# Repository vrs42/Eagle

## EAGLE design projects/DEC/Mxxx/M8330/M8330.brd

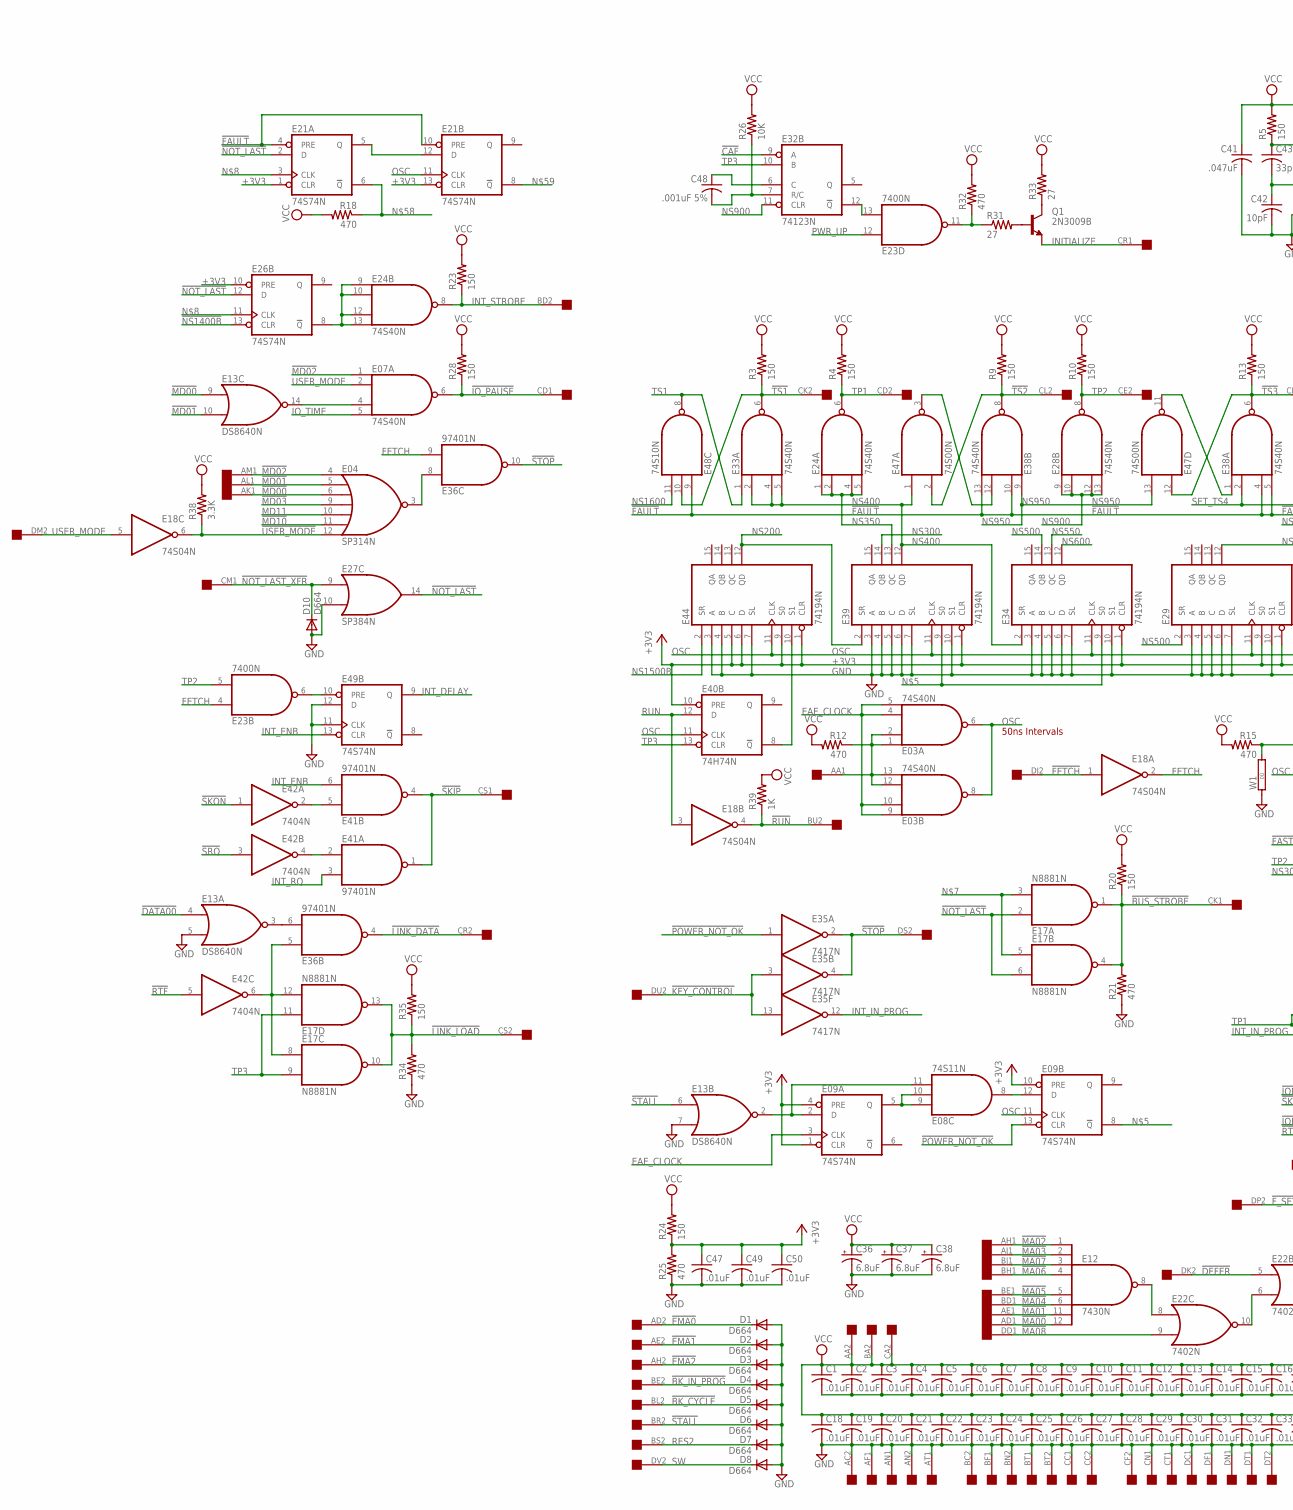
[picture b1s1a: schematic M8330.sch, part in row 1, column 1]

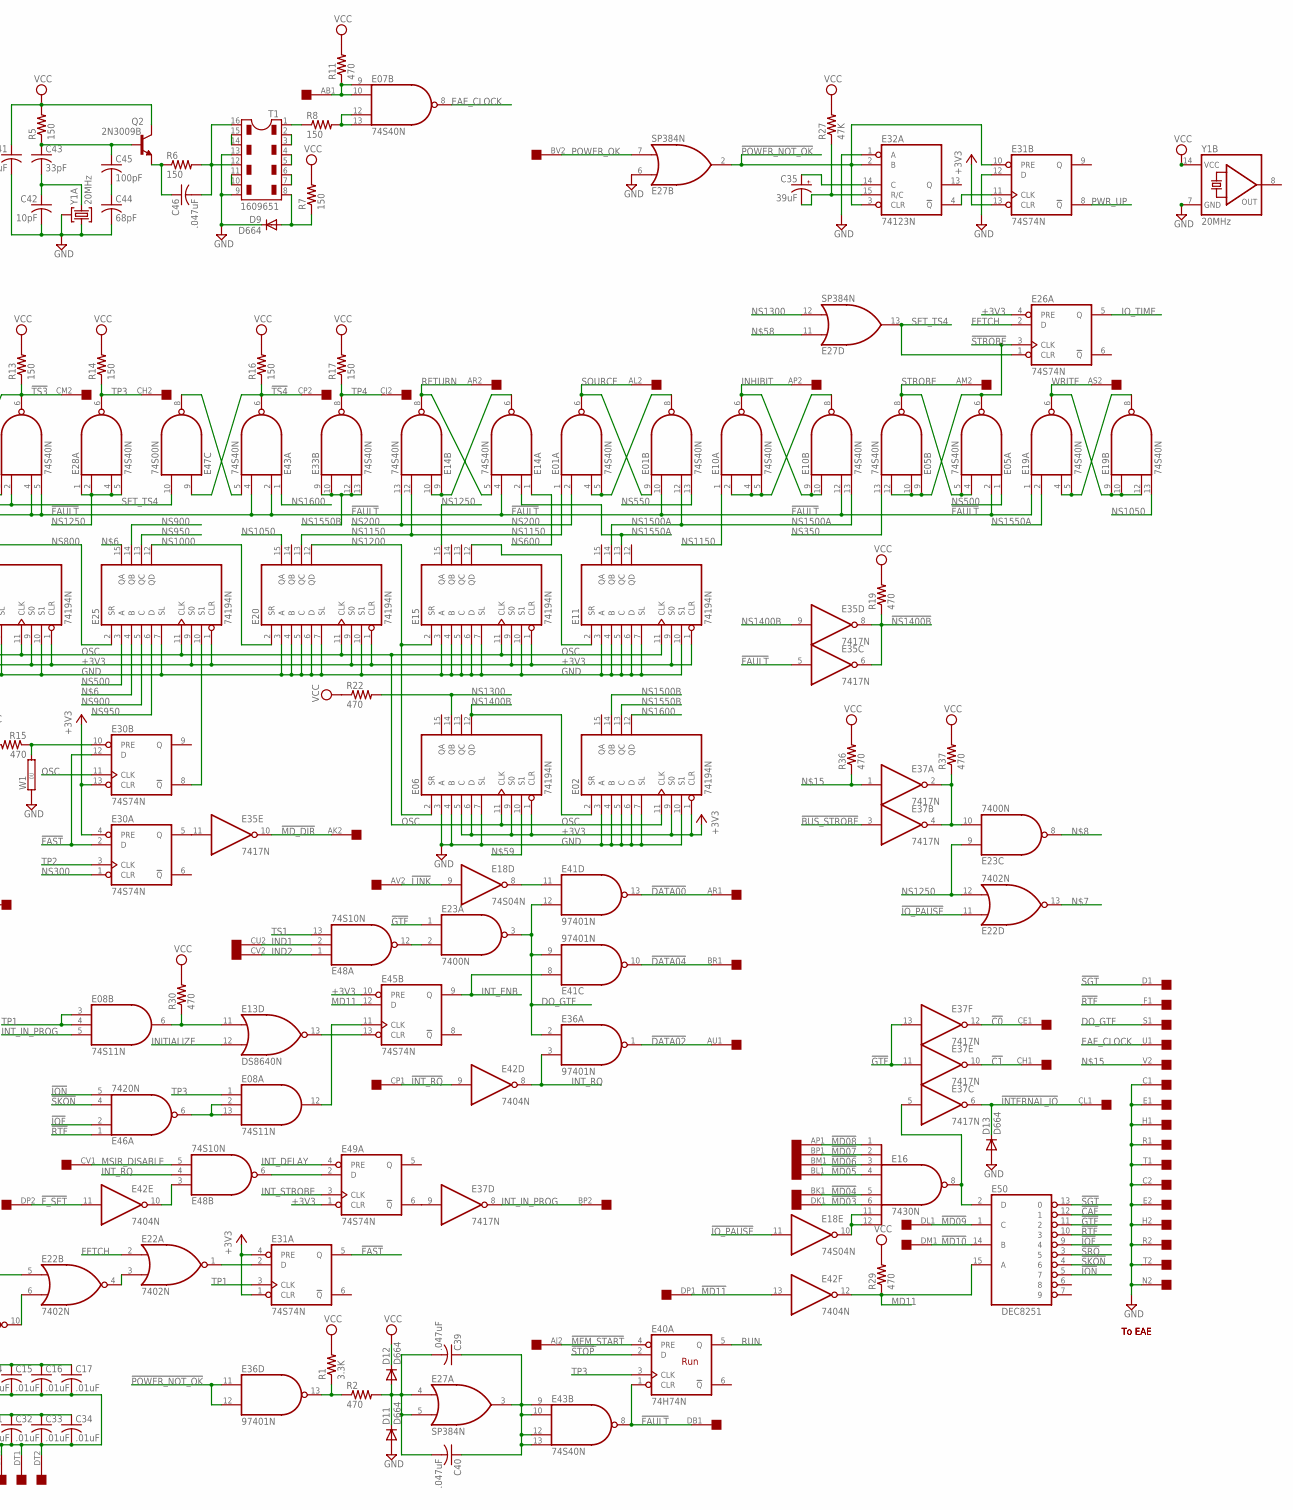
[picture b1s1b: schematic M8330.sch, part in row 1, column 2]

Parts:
C1, C2, C3, C4, C5, C6, C7, C8, C9, C10, C11, C12, C13, C14, C15, C16, C17, C18, C19, C20, C21, C22, C23, C24, C25, C26, C27, C28, C29, C30, C31, C32, C33, C34, C47, C49, C50: .01uF; C050-025X075
C35: 39uF; E12-8
C36, C37, C38: 6.8uF; E12-8
C39, C40, C41, C46: .047uF; C050-025X075
C42: 10pF; C050-025X075
C43: 33pF; C050-025X075
C44: 68pF; C050-025X075
C45: 100pF; C050-025X075
C48: .001uF 5%; C050-025X075
D1, D2, D3, D4, D5, D6, D7, D8, D9, D10, D11, D12, D13: D664; DO35-10
E01, E03, E05, E07, E10, E14, E19, E24, E28, E33, E38, E43: 74S40N; DIL14
E02, E06, E11, E15, E20, E25, E29, E34, E39, E44: 74194N; DIL16
E04: SP314N; DIL14
E08: 74S11N; DIL14
E09, E21, E26, E30, E31, E45, E49: 74S74N; DIL14
E12, E16: 7430N; DIL14
E13: DS8640N; DIL14
E17: N8881N; DIL14
E18: 74S04N; DIL14
E22: 7402N; DIL14
E23: 7400N; DIL14
E27: SP384N; DIL14
E32: 74123N; DIL16
E35, E37: 7417N; DIL14
E36, E41: 97401N; DIL14
E40: 74H74N; DIL14
E42: 7404N; DIL14
E46: 7420N; DIL14
E47: 74S00N; DIL14
E48: 74S10N; DIL14
E50: DEC8251; DIL16
J: SINGLE; EDGE-CON2
Q1, Q2: 2N3009B; TO5
R1, R38: 3.3K; 0207/10
R2, R11, R12, R15, R18, R19, R21, R22, R25, R29, R30, R32, R34, R36, R37: 470; 0207/10
R3, R4, R5, R6, R7, R8, R9, R10, R13, R14, R16, R17, R20, R23, R24, R28, R35: 150; 0207/10
R26: 10K; 0207/10
R27: 47K; 0207/10
R31, R33: 27; 0207/10
R39: 1K; 0207/10
T1: 1609651; DIL16
U$2: QUAD; EDGE-CON8
W1: 0R; 0R/10
Y1A: 20MHz; HC49TL-H
Y1B: 20MHz; DIL14S

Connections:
!BK_CYCLE: D5.C, U$2.BL2
!BK_IN_PROG: D4.C, U$2.BE2
!BUS_STROBE: E17.1 (O), E17.4 (O), E37.3 (I), R20.1, R21.2, U$2.CK1
!C0: E37.12 (O), U$2.CE1
!C1: E37.10 (O), U$2.CH1
!CAF: E32.9 (A), E50.12 (1)
!DATA00: E13.4 (I0), E41.13 (O), U$2.AR1
!DATA02: E36.1 (O), U$2.AU1
!DATA04: E41.10 (O), U$2.BR1
!DEFER: E22.5 (I0), U$2.DK2
!EMA0: D1.C, U$2.AD2
!EMA1: D2.C, U$2.AE2
!EMA2: D3.C, U$2.AH2
!FAST: E30.2 (D), E30.12 (D), E31.5 (Q)
!FAULT: E01.10 (I1), E05.2 (I1), E10.12 (I2), E14.4 (I2), E19.1 (I0), E21.4 (PRE), E21.10 (PRE), E35.5 (I), E38.4 (I2), E38.5 (I3), E38.10 (I1), E38.13 (I3), E40.1 (CLR), E43.2 (I1), E43.4 (I2), E43.8 (O), E48.9 (I0), U$2.DB1
!FETCH: E18.1 (I), U$2.DJ2
!F_SET: E42.11 (I), U$2.DP2
!GTF: E23.1 (I0), E37.11 (I), E37.13 (I), E50.11 (2)
!INTERNAL_IO: D13.C, E37.6 (O), U$2.CL1
!INT_RQ: E42.9 (I), U$2.CP1
!IOF: E46.2 (I1), E50.9 (4)
!ION: E46.5 (I3), E50.5 (7)
!IO_PAUSE: E07.6 (O), E18.11 (I), E22.11 (I0), R28.1, U$2.CD1
!KEY_CONTROL: E35.3 (I), E35.13 (I), U$2.DU2
!LINK: E18.9 (I), U$2.AV2
!LINK_DATA: E36.4 (O), U$2.CR2
!LINK_LOAD: E17.10 (O), E17.13 (O), R34.2, R35.1, U$2.CS2
!MA00: E12.12 (I7), U$2.AD1
!MA01: E12.11 (I6), U$2.AE1
!MA02: E12.1 (I0), U$2.AH1
!MA03: E12.2 (I1), U$2.AJ1
!MA04: E12.6 (I5), U$2.BD1
!MA05: E12.5 (I4), U$2.BE1
!MA06: E12.4 (I3), U$2.BH1
!MA07: E12.3 (I2), U$2.BJ1
!MA08: E22.9 (I1), U$2.DD1
!MD00: E04.6 (I2), E13.9 (I0), U$2.AK1
!MD01: E04.5 (I1), E13.10 (I1), U$2.AL1
!MD02: E04.4 (I0), E07.1 (I0), U$2.AM1
!MD03: E04.9 (I3), E16.6 (I5), U$2.DK1
!MD04: E16.5 (I4), U$2.BK1
!MD05: E16.4 (I3), U$2.BL1
!MD06: E16.3 (I2), U$2.BM1
!MD07: E16.2 (I1), U$2.BP1
!MD08: E16.1 (I0), U$2.AP1
!MD09: E50.1 (C), U$2.DL1
!MD10: E04.11 (I5), E50.14 (B), U$2.DM1
!MD11: E42.13 (I), U$2.DP1
!MD_DIR: E35.10 (O), U$2.AK2
!MEM_START: E40.4 (PRE), U$2.AJ2
!NOT_LAST: E17.2 (I0), E17.6 (I1), E21.2 (D), E26.12 (D), E27.14 (O)
!NOT_LAST_XFR: D10.C, E27.9 (I0), U$2.CM1
!NS1400B: E26.13 (CLR), E35.6 (O), E35.8 (O), R19.1
!POWER_NOT_OK: E09.13 (CLR), E27.2 (O), E31.10 (PRE), E32.2 (B), E32.3 (CLR), E35.1 (I), E36.11 (I0), E36.12 (I1)
!RTF: E42.5 (I), E46.1 (I0), E50.10 (3), J.F1
!RUN: E18.4 (O), R39.1, U$2.BU2
!SGT: E50.13 (0), J.D1
!SKIP: E41.1 (O), E41.4 (O), U$2.CS1
!SKON: E42.1 (I), E46.4 (I2), E50.4 (6)
!SRQ: E42.3 (I), E50.3 (5)
!STALL: D6.C, E13.6 (I0), U$2.BR2
!STOP: E35.2 (O), E35.4 (O), E36.10 (O), E40.2 (D), U$2.DS2
!STROBE: E05.6 (O), E05.9 (I0), E05.10 (I1), E05.12 (I2), E26.3 (CLK)
!TS1: E33.6 (O), E48.10 (I1), R3.1, U$2.CK2
!TS2: E38.8 (O), E47.2 (I1), R9.1, U$2.CL2
!TS3: E38.6 (O), E47.12 (I0), R13.1, U$2.CM2
!TS4: E43.6 (O), E47.9 (I0), R16.1, U$2.CP2
!USER_MODE: E04.12 (I6), E18.6 (O), R38.1
+3V3: C47.1, C49.1, C50.1, E02.1 (CLR), E02.9 (S0), E06.1 (CLR), E06.5 (C), E06.6 (D), E06.9 (S0), E09.1 (CLR), E09.4 (PRE), E09.10 (PRE), E11.1 (CLR), E11.9 (S0), E15.1 (CLR), E15.9 (S0), E20.1 (CLR), E20.9 (S0), E21.1 (CLR), E21.13 (CLR), E25.1 (CLR), E25.9 (S0), E26.4 (PRE), E26.10 (PRE), E29.1 (CLR), E29.9 (S0), E30.4 (PRE), E30.13 (CLR), E31.1 (CLR), E31.4 (PRE), E31.13 (CLR), E34.1 (CLR), E39.1 (CLR), E40.10 (PRE), E44.1 (CLR), E44.5 (C), E44.6 (D), E44.9 (S0), E45.10 (PRE), E49.1 (CLR), R24.1, R25.2
DO_GTF: E23.3 (O), E36.2 (I0), E41.9 (I1), E41.12 (I1), J.S1
EAE_CLOCK: E03.4 (I2), E03.5 (I3), E03.9 (I0), E03.10 (I1), E07.8 (O), E09.3 (CLK), J.U1
FETCH: E18.2 (O), E22.2 (I0), E23.4 (I0), E26.2 (D), E36.9 (I1)
F_SET: E42.10 (O), E48.3 (I0)
GND: C1.2, C2.2, C3.2, C4.2, C5.2, C6.2, C7.2, C8.2, C9.2, C10.2, C11.2, C12.2, C13.2, C14.2, C15.2, C16.2, C17.2, C18.2, C19.2, C20.2, C21.2, C22.2, C23.2, C24.2, C25.2, C26.2, C27.2, C28.2, C29.2, C30.2, C31.2, C32.2, C33.2, C34.2, C36.-, C37.-, C38.-, C41.2, C42.2, C44.2, C47.2, C49.2, C50.2, D1.A, D2.A, D3.A, D4.A, D5.A, D6.A, D7.A, D8.A, D9.C, D10.A, D11.A, D13.A, E01.7 (GND), E02.3 (A), E02.4 (B), E02.5 (C), E02.6 (D), E02.7 (SL), E02.8 (GND), E02.10 (S1), E03.7 (GND), E04.1 (GND), E05.7 (GND), E06.3 (A), E06.4 (B), E06.7 (SL), E06.8 (GND), E07.7 (GND), E08.7 (GND), E09.7 (GND), E10.7 (GND), E11.3 (A), E11.4 (B), E11.5 (C), E11.6 (D), E11.7 (SL), E11.8 (GND), E11.10 (S1), E12.7 (GND), E13.1 (GND), E13.5 (I1), E13.7 (I1), E14.7 (GND), E15.3 (A), E15.4 (B), E15.5 (C), E15.6 (D), E15.7 (SL), E15.8 (GND), E15.10 (S1), E16.7 (GND), E17.7 (GND), E18.7 (GND), E19.7 (GND), E20.3 (A), E20.4 (B), E20.5 (C), E20.6 (D), E20.7 (SL), E20.8 (GND), E20.10 (S1), E21.7 (GND), E22.7 (GND), E23.7 (GND), E24.7 (GND), E25.7 (SL), E25.8 (GND), E26.7 (GND), E27.1 (GND), E27.6 (I0), E27.10 (I1), E28.7 (GND), E29.3 (A), E29.4 (B), E29.5 (C), E29.6 (D), E29.7 (SL), E29.8 (GND), E29.10 (S1), E30.7 (GND), E31.7 (GND), E31.12 (D), E32.1 (A), E32.8 (GND), E33.7 (GND), E34.3 (A), E34.4 (B), E34.5 (C), E34.6 (D), E34.7 (SL), E34.8 (GND), E34.10 (S1), E35.7 (GND), E36.7 (GND), E37.7 (GND), E38.7 (GND), E39.3 (A), E39.4 (B), E39.5 (C), E39.6 (D), E39.7 (SL), E39.8 (GND), E39.10 (S1), E40.7 (GND), E41.7 (GND), E42.7 (GND), E43.7 (GND), E44.3 (A), E44.4 (B), E44.7 (SL), E44.8 (GND), E45.7 (GND), E46.7 (GND), E47.7 (GND), E48.7 (GND), E49.7 (GND), E49.11 (CLK), E49.12 (D), E50.8 (GND), J.C1, J.C2, J.E1, J.E2, J.H1, J.H2, J.N2, J.R1, J.R2, J.T1, J.T2, R21.1, R25.1, R34.1, T1.9, T1.13, U$2.AC2, U$2.AF1, U$2.AN1, U$2.AN2, U$2.AT1, U$2.BC2, U$2.BF1, U$2.BN2, U$2.BT1, U$2.BT2, U$2.CC1, U$2.CC2, U$2.CF2, U$2.CN1, U$2.CT1, U$2.DC1, U$2.DF1, U$2.DN1, U$2.DT1, U$2.DT2, W1.1, Y1A.1, Y1A.3, Y1B.7 (GND)
IND1: E48.2 (I1), U$2.CU2
IND2: E48.1 (I0), U$2.CV2
INHIBIT: E10.6 (O), E10.9 (I0), E10.10 (I1), U$2.AP2
INITIALIZE: E13.12 (I1), Q1.1 (E), U$2.CR1
INT_DELAY: E49.4 (PRE), E49.9 (Q)
INT_ENB: E41.6 (I1), E41.8 (I0), E45.9 (Q), E49.13 (CLR)
INT_IN_PROG: E08.5 (I2), E35.12 (O), E37.8 (O), U$2.BP2
INT_RQ: E36.3 (I1), E41.3 (I1), E42.8 (O), E48.4 (I1)
INT_STROBE: E24.8 (O), E49.3 (CLK), R23.1, U$2.BD2
IO_TIME: E07.5 (I3), E26.5 (Q)
MD11: E04.10 (I4), E42.12 (O), E45.12 (D), E50.15 (A), R29.1
MSIR_DISABLE: E48.5 (I2), U$2.CV1
unnamed: E16.8 (O), E37.5 (I), E50.2 (D)
unnamed: E23.10 (I1), E37.2 (O), E37.4 (O), R37.1
unnamed: E04.3 (O), E36.8 (I0)
unnamed: E40.8 (!Q), E44.10 (S1)
unnamed: E09.8 (!Q), E34.9 (S0), E39.9 (S0)
unnamed: E25.4 (B), E25.15 (QA)
unnamed: E17.3 (I1), E17.5 (I0), E22.13 (O)
unnamed: E21.3 (CLK), E23.8 (O), E26.11 (CLK)
unnamed: E18.8 (O), E41.11 (I0)
unnamed: C42.1, C43.2, Y1A.2
unnamed: E03.1 (I0), E03.2 (I1), E03.12 (I2), E03.13 (I3), R12.1, U$2.AA1
unnamed: E07.9 (I0), E07.10 (I1), R11.1, U$2.AB1
unnamed: E12.8 (O), E22.8 (I0)
unnamed: E37.1 (I), J.V2, R36.1
unnamed: E08.11 (I2), E09.2 (D), E13.2 (O)
unnamed: C48.2, E32.7 (R/C), R26.1
unnamed: E16.11 (I6), E16.12 (I7), E18.10 (O)
unnamed: E23.13 (I1), E32.12 (!Q)
unnamed: C48.1, E32.6 (C)
unnamed: Q1.3 (C), R33.1
unnamed: Q1.2 (B), R31.2
unnamed: E23.11 (O), R31.1, R32.1
unnamed: E31.11 (CLK), E32.4 (!Q)
unnamed: C43.1, C45.1, Q2.2 (B), R5.1
unnamed: C39.1, C40.1, E27.3 (O), E43.9 (I0), E43.10 (I1), E43.12 (I2), E43.13 (I3)
unnamed: C39.2, C40.2, D11.C, D12.A, E27.4 (I0), E27.5 (I1), R2.2
unnamed: C46.2, R6.2, T1.12, T1.16
unnamed: E36.13 (O), R1.1, R2.1
unnamed: C44.1, C45.2
unnamed: C46.1, Q2.1 (E), R6.1
unnamed: R8.1, T1.1
unnamed: T1.10, T1.11
unnamed: T1.6, T1.7
unnamed: T1.14, T1.15
unnamed: T1.2, T1.3
unnamed: T1.4, T1.5
unnamed: D9.A, R7.1, T1.8
unnamed: E07.12 (I2), E07.13 (I3), R8.2
unnamed: E22.6 (I1), E22.10 (O)
unnamed: E08.9 (I0), E08.10 (I1), E09.5 (Q)
unnamed: E08.8 (O), E09.12 (D)
unnamed: E38.12 (I2), E47.3 (O)
unnamed: C35.+, E32.14 (C)
unnamed: C35.-, E32.15 (R/C), R27.1
unnamed: E38.1 (I0), E47.11 (O)
unnamed: E14.6 (O), E14.9 (I0), E14.10 (I1)
unnamed: E10.2 (I1), E10.4 (I2), E10.5 (I3), E10.8 (O)
unnamed: E43.5 (I3), E47.8 (O)
unnamed: E01.4 (I2), E01.5 (I3), E01.8 (O)
unnamed: E25.10 (S1), E30.8 (!Q)
unnamed: E30.5 (Q), E35.11 (I)
unnamed: E19.4 (I2), E19.5 (I3), E19.8 (O)
unnamed: E30.10 (PRE), R15.1, W1.2
unnamed: E21.5 (Q), E21.12 (D)
unnamed: E21.6 (!Q), E27.11 (I0), R18.1
unnamed: E06.10 (S1), E21.8 (!Q)
unnamed: E24.9 (I0), E24.10 (I1), E24.12 (I2), E24.13 (I3), E26.8 (!Q)
unnamed: E22.1 (O), E31.2 (D)
unnamed: E07.4 (I2), E13.14 (O)
unnamed: E22.3 (I1), E22.4 (O)
unnamed: E23.2 (I1), E48.12 (O)
unnamed: E08.12 (O), E45.11 (CLK)
unnamed: E08.6 (O), E13.11 (I0), R30.1
unnamed: E37.9 (I), E49.6 (!Q)
unnamed: E13.13 (O), E45.13 (CLR)
unnamed: E08.2 (I1), E08.13 (I2), E46.6 (O)
unnamed: E41.5 (I0), E42.2 (O)
unnamed: E23.6 (O), E49.10 (PRE)
unnamed: E48.6 (O), E49.2 (D)
unnamed: E41.2 (I0), E42.4 (O)
unnamed: E17.8 (I0), E17.12 (I1), E36.5 (I0), E42.6 (O)
unnamed: E13.3 (O), E36.6 (I1)
NS200: E01.2 (I1), E14.13 (I3), E39.2 (SR), E44.12 (QD)
NS300: E30.1 (CLR), E39.14 (QB)
NS350: E05.13 (I3), E24.1 (I0), E24.2 (I1), E24.4 (I2), E24.5 (I3), E39.13 (QC)
NS400: E33.2 (I1), E33.4 (I2), E33.5 (I3), E34.2 (SR), E39.12 (QD), E47.1 (I0)
NS500: E05.1 (I0), E25.3 (A), E29.2 (SR), E34.14 (QB)
NS550: E01.13 (I3), E34.13 (QC)
NS600: E14.1 (I0), E34.12 (QD)
NS800: E25.2 (SR), E29.12 (QD)
NS900: E25.5 (C), E25.14 (QB), E28.9 (I0), E28.10 (I1), E28.12 (I2), E28.13 (I3), E32.11 (CLR)
NS950: E25.6 (D), E25.13 (QC), E38.9 (I0), E47.13 (I1)
NS1000: E20.2 (SR), E25.12 (QD)
NS1050: E19.13 (I3), E20.15 (QA)
NS1150: E01.1 (I0), E10.1 (I0), E14.12 (I2), E20.13 (QC)
NS1200: E06.2 (SR), E15.2 (SR), E20.12 (QD)
NS1250: E15.15 (QA), E22.12 (I1), E23.9 (I0), E28.1 (I0), E28.2 (I1), E28.4 (I2), E28.5 (I3)
NS1300: E06.14 (QB), E27.12 (I1), R22.2
NS1400A: E11.2 (SR), E15.12 (QD)
NS1400B: E02.2 (SR), E06.12 (QD), E35.9 (I)
NS1500A: E01.12 (I2), E10.13 (I3), E11.14 (QB)
NS1500B: E02.14 (QB), E44.2 (SR)
NS1550A: E11.13 (QC), E14.2 (I1), E19.2 (I1)
NS1550B: E02.13 (QC), E33.9 (I0), E33.10 (I1), E33.12 (I2), E33.13 (I3)
NS1600: E02.12 (QD), E43.1 (I0), E48.11 (I2)
OSC: E02.11 (CLK), E03.6 (O), E03.8 (O), E06.11 (CLK), E09.11 (CLK), E11.11 (CLK), E15.11 (CLK), E20.11 (CLK), E21.11 (CLK), E25.11 (CLK), E29.11 (CLK), E30.11 (CLK), E34.11 (CLK), E39.11 (CLK), E40.11 (CLK), E44.11 (CLK)
POWER_OK: E27.7 (I1), U$2.BV2
PWR_UP: E23.12 (I0), E31.8 (!Q)
RES2: D7.C, U$2.BS2
RETURN: E14.5 (I3), E14.8 (O), U$2.AR2
RUN: E18.3 (I), E40.5 (Q), E40.12 (D)
SET_TS4: E26.1 (CLR), E27.13 (O), E38.2 (I1), E47.10 (I1)
SOURCE: E01.6 (O), E01.9 (I0), U$2.AL2
STROBE: E05.4 (I2), E05.5 (I3), E05.8 (O), U$2.AM2
SW: D8.C, U$2.DV2
TP1: E08.3 (I0), E08.4 (I1), E24.6 (O), E31.3 (CLK), R4.1, U$2.CD2
TP2: E23.5 (I1), E28.8 (O), E30.3 (CLK), R10.1, U$2.CE2
TP3: E08.1 (I0), E17.9 (I1), E17.11 (I0), E28.6 (O), E32.10 (B), E40.3 (CLK), E40.13 (CLR), R14.1, U$2.CH2
TP4: E33.8 (O), R17.1, U$2.CJ2
TS1: E33.1 (I0), E48.8 (O), E48.13 (I2)
USER_MODE: E07.2 (I1), E18.5 (I), U$2.DM2
VCC: C1.1, C2.1, C3.1, C4.1, C5.1, C6.1, C7.1, C8.1, C9.1, C10.1, C11.1, C12.1, C13.1, C14.1, C15.1, C16.1, C17.1, C18.1, C19.1, C20.1, C21.1, C22.1, C23.1, C24.1, C25.1, C26.1, C27.1, C28.1, C29.1, C30.1, C31.1, C32.1, C33.1, C34.1, C36.+, C37.+, C38.+, C41.1, D12.C, E01.14 (VCC), E02.16 (VCC), E03.14 (VCC), E04.8 (VCC), E05.14 (VCC), E06.16 (VCC), E07.14 (VCC), E08.14 (VCC), E09.14 (VCC), E10.14 (VCC), E11.16 (VCC), E12.14 (VCC), E13.8 (VCC), E14.14 (VCC), E15.16 (VCC), E16.14 (VCC), E17.14 (VCC), E18.14 (VCC), E19.14 (VCC), E20.16 (VCC), E21.14 (VCC), E22.14 (VCC), E23.14 (VCC), E24.14 (VCC), E25.16 (VCC), E26.14 (VCC), E27.8 (VCC), E28.14 (VCC), E29.16 (VCC), E30.14 (VCC), E31.14 (VCC), E32.16 (VCC), E33.14 (VCC), E34.16 (VCC), E35.14 (VCC), E36.14 (VCC), E37.14 (VCC), E38.14 (VCC), E39.16 (VCC), E40.14 (VCC), E41.14 (VCC), E42.14 (VCC), E43.14 (VCC), E44.16 (VCC), E45.14 (VCC), E46.14 (VCC), E47.14 (VCC), E48.14 (VCC), E49.14 (VCC), E50.16 (VCC), Q2.3 (C), R1.2, R3.2, R4.2, R5.2, R7.2, R9.2, R10.2, R11.2, R12.2, R13.2, R14.2, R15.2, R16.2, R17.2, R18.2, R19.2, R20.2, R22.1, R23.2, R24.2, R26.2, R27.2, R28.2, R29.2, R30.2, R32.2, R33.2, R35.2, R36.2, R37.2, R38.2, R39.2, U$2.AA2, U$2.BA2, U$2.CA2, Y1B.14 (VCC)
WRITE: E19.6 (O), E19.9 (I0), E19.10 (I1), E19.12 (I2), U$2.AS2

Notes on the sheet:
Run
To EAE
50ns Intervals

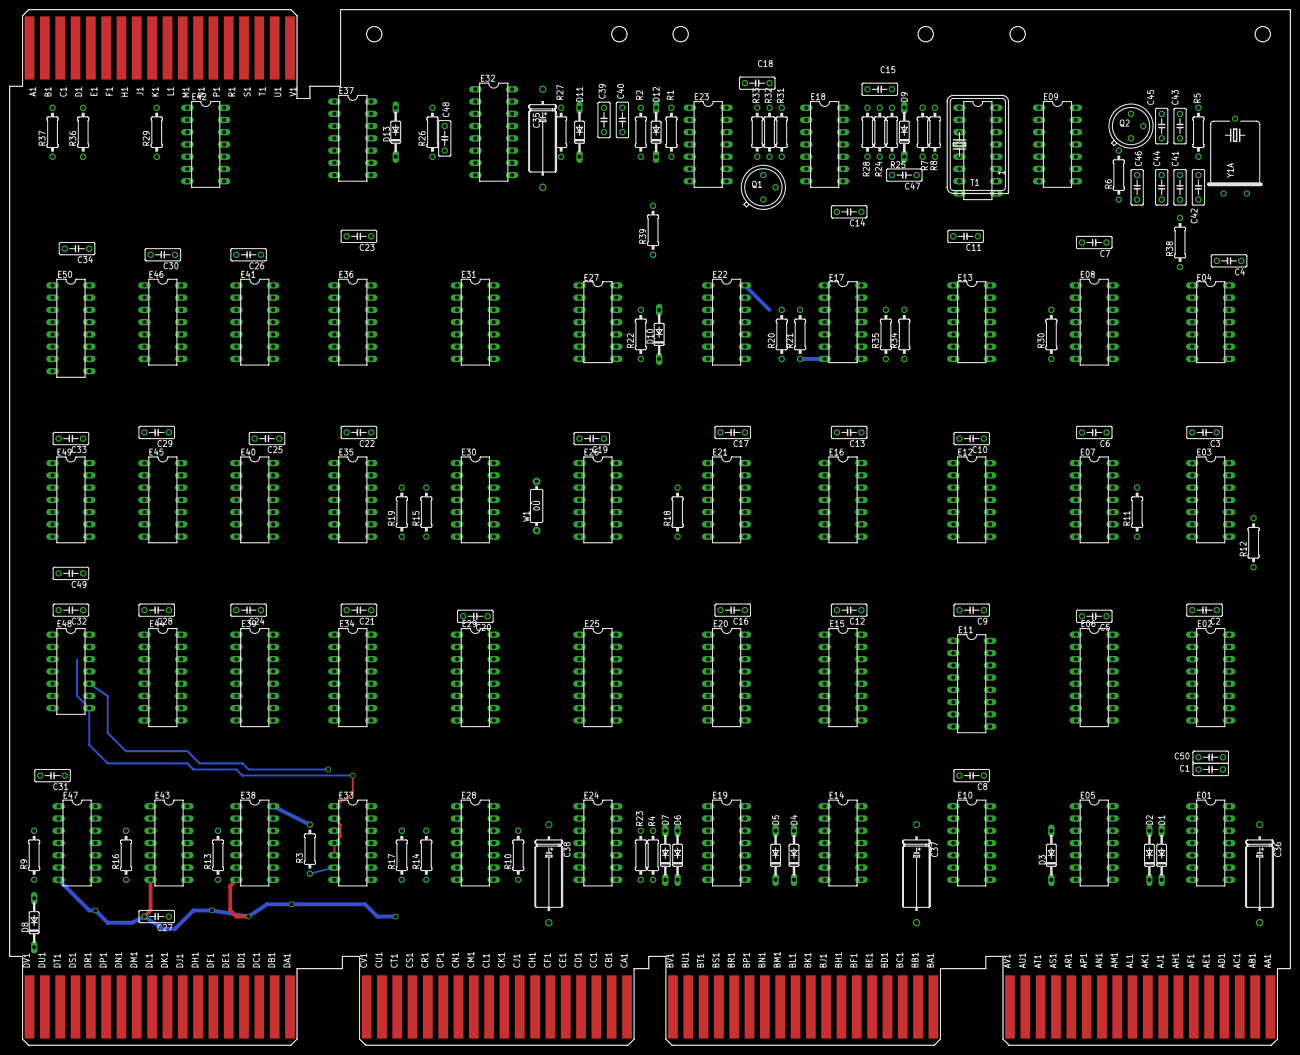
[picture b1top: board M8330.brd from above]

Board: 2 copper layers, 265.4 x 214.6 mm, 160 parts (0 on the bottom side), 199 nets.

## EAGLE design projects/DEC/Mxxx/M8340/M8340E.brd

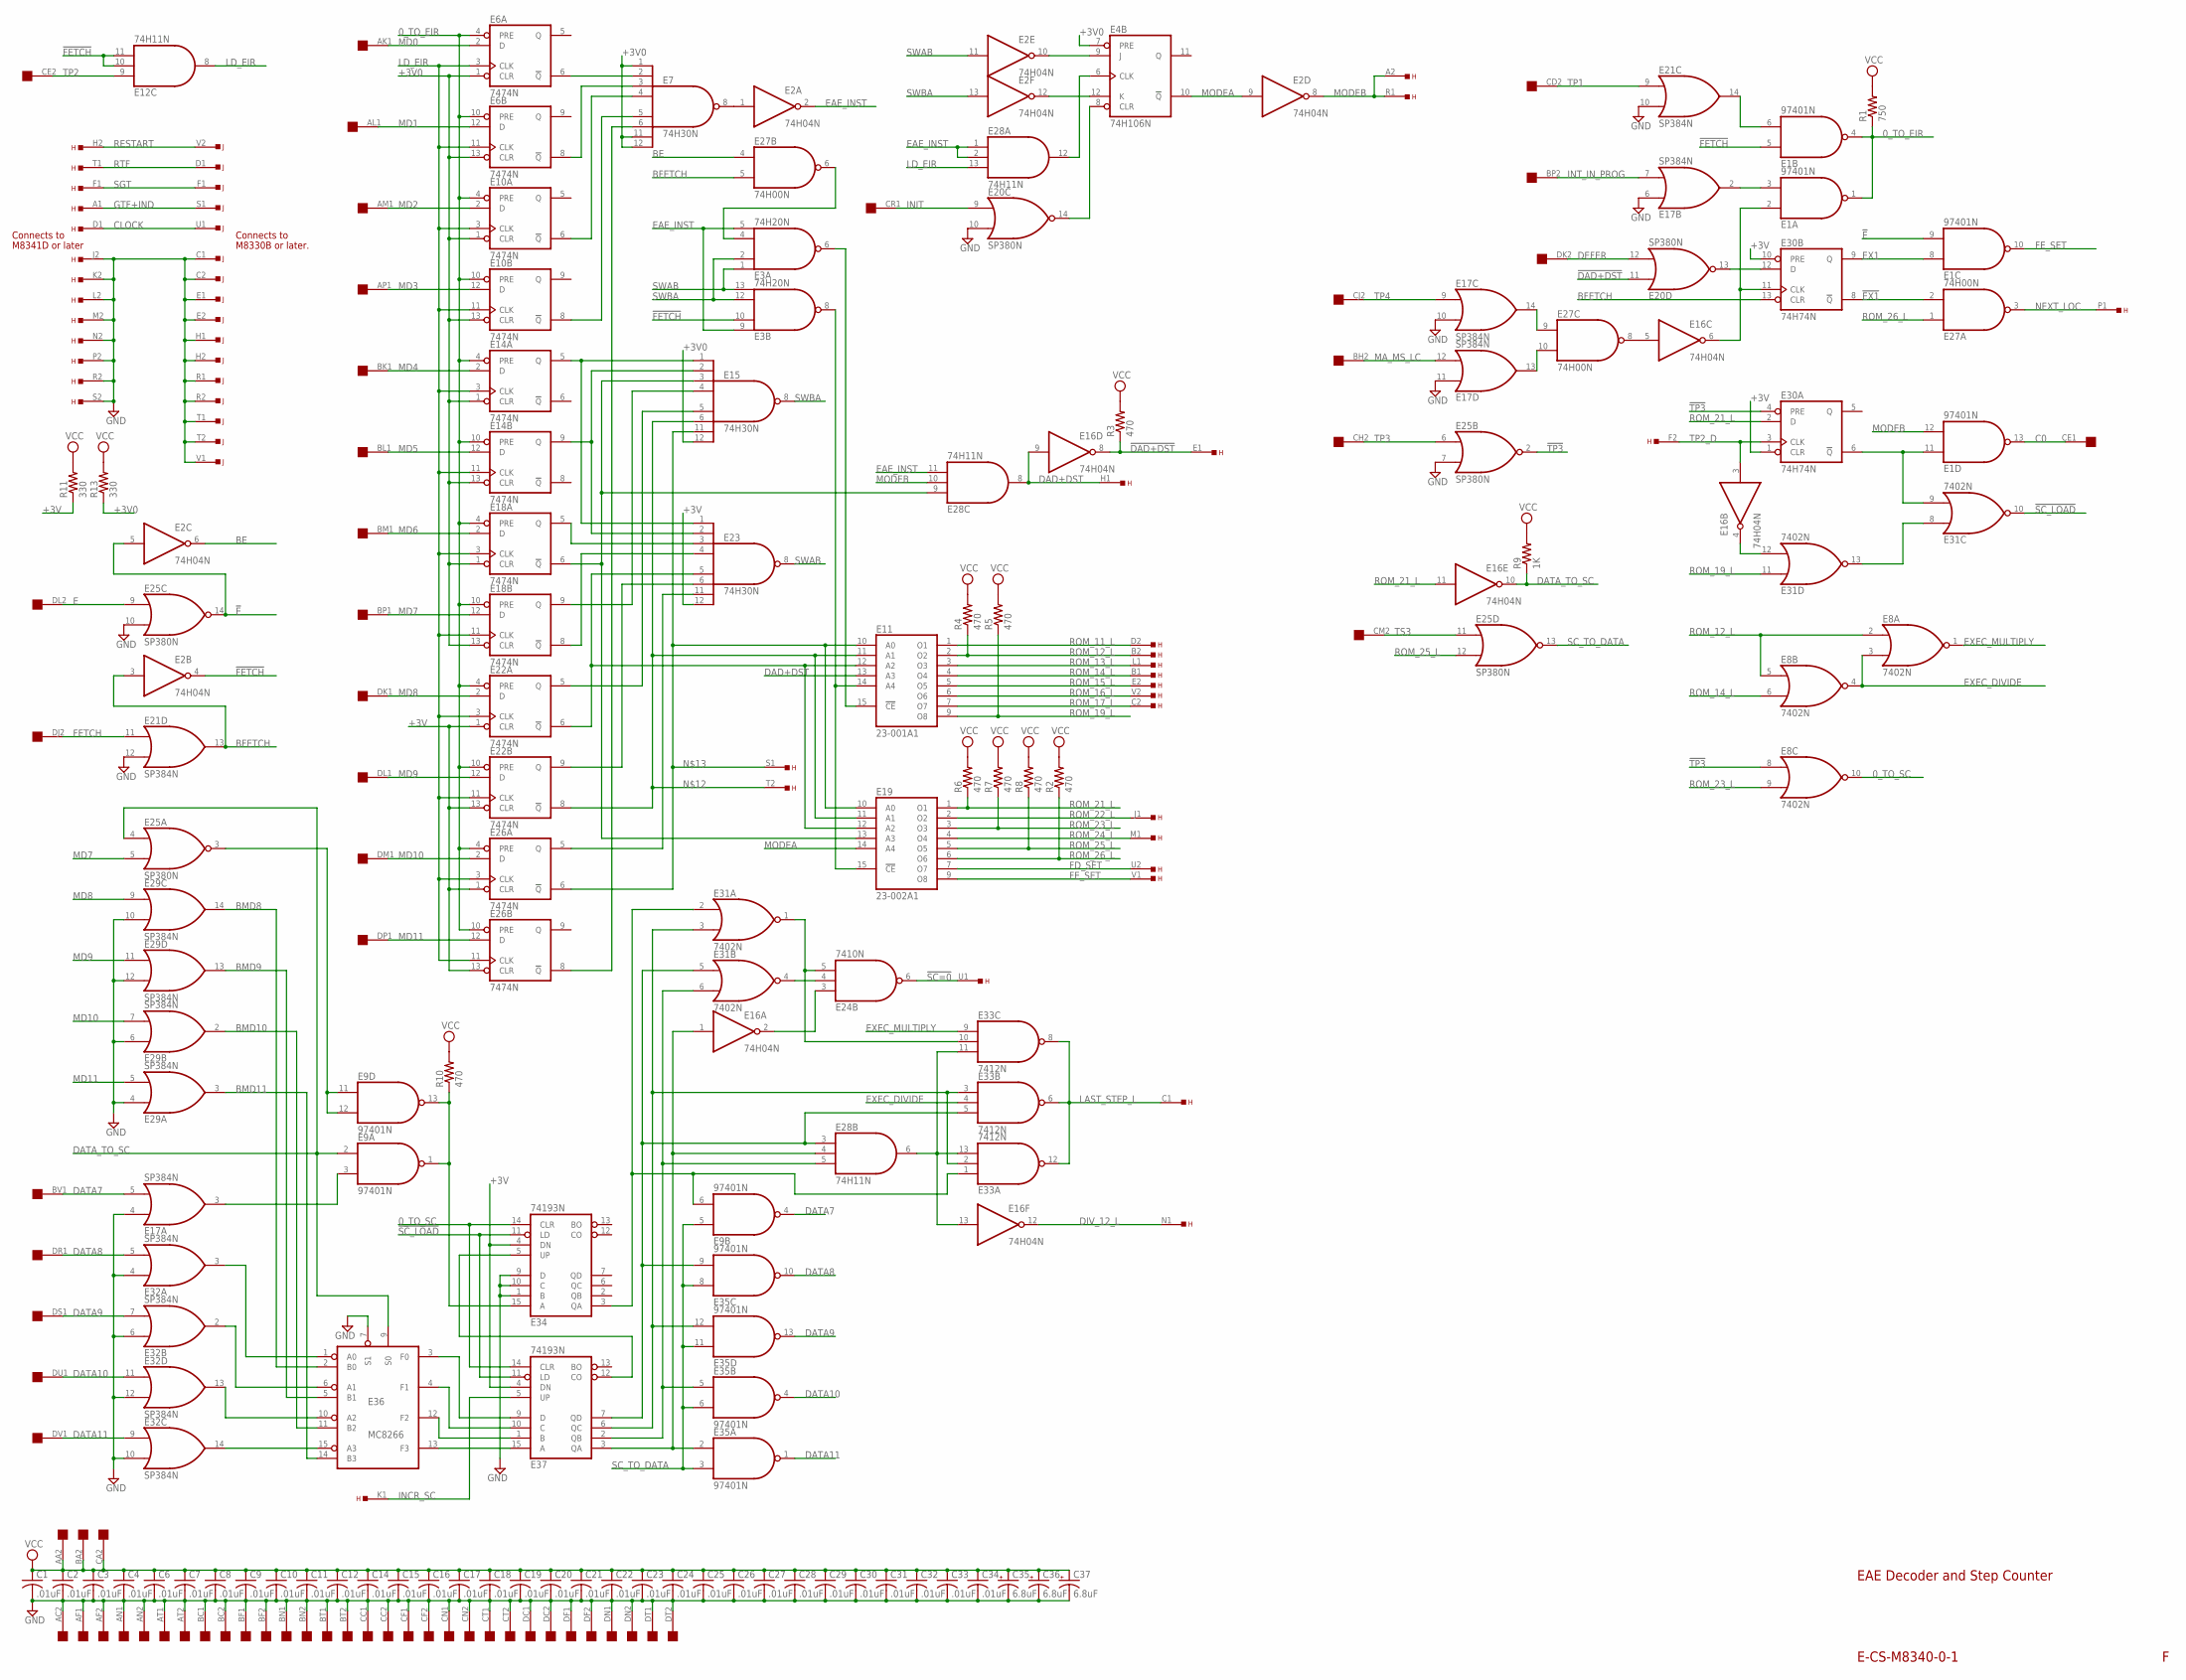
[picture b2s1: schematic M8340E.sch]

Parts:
C1, C2, C3, C4, C6, C7, C8, C9, C10, C11, C12, C14, C15, C16, C17, C18, C19, C20, C21, C22, C23, C24, C25, C26, C27, C28, C29, C30, C31, C32, C33, C34: .01uF; C063-025X075
C35, C36, C37: 6.8uF; E12-8
E1, E9, E35: 97401N; DIL14
E2, E16: 74H04N; DIL14
E3: 74H20N; DIL14
E4: 74H106N; DIL16
E6, E10, E14, E18, E22, E26: 7474N; DIL14
E7, E15, E23: 74H30N; DIL14
E8, E31: 7402N; DIL14
E11: 23-001A1; DIL16
E12, E28: 74H11N; DIL14
E17, E21, E29, E32: SP384N; DIL14
E19: 23-002A1; DIL16
E20, E25: SP380N; DIL14
E24: 7410N; DIL14
E27: 74H00N; DIL14
E30: 74H74N; DIL14
E33: 7412N; DIL14
E34, E37: 74193N; DIL16
E36: MC8266; DIL16
H: EDGE-TOP; EDGE-CON2
J: EDGE-TOP; EDGE-CON2
R1: 750; 0207/10
R2, R3, R4, R5, R6, R7, R8, R10: 470; 0207/10
R9: 1K; 0207/10
R11, R13: 330; 0207/10
U$2: QUAD; EDGE-CON8

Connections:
0_TO_EIR: E1.1 (O), E1.4 (O), E6.4 (PRE), E6.10 (PRE), E10.4 (PRE), E10.10 (PRE), E14.4 (PRE), E14.10 (PRE), E18.4 (PRE), E18.10 (PRE), E22.4 (PRE), E22.10 (PRE), E26.4 (PRE), E26.10 (PRE), R1.1
0_TO_SC: E8.10 (O), E34.14 (CLR), E37.14 (CLR)
!ADLK_DIS: E11.6 (O6), H.V2
!DAD+DST: E16.8 (O), E20.11 (I0), H.E1, R3.1
!E: E1.9 (I1), E2.5 (I), E25.14 (O)
!EX1: E27.2 (I1), E30.8 (!Q)
!FETCH: E1.5 (I0), E2.4 (O), E3.10 (I1), E12.10 (I1), E12.11 (I2)
!INIT: E4.8 (CLR), E20.14 (O)
!SC_0: E24.6 (O), H.U1
!SC_LOAD: E31.10 (O), E34.11 (LD), E37.11 (LD)
!SGT: H.F1, J.F1
!TP3: E8.8 (I0), E25.2 (O), E30.4 (PRE)
+3V: E22.1 (CLR), E22.13 (CLR), E23.12 (I7), E26.1 (CLR), E26.13 (CLR), E30.1 (CLR), E30.10 (PRE), E34.4 (DN), E37.4 (DN), R11.1
+3V0: E4.7 (PRE), E6.1 (CLR), E6.13 (CLR), E7.1 (I0), E7.11 (I6), E7.12 (I7), E10.1 (CLR), E10.13 (CLR), E14.1 (CLR), E14.13 (CLR), E15.12 (I7), E18.1 (CLR), E18.13 (CLR), R13.1
BE: E2.6 (O), E27.4 (I0)
BFETCH: E2.3 (I), E21.13 (O), E27.5 (I1), E30.13 (CLR)
BMD8: E29.14 (O), E36.2 (B0)
BMD9: E29.13 (O), E36.5 (B1)
BMD10: E29.2 (O), E36.11 (B2)
BMD11: E29.3 (O), E36.14 (B3)
C0: E1.13 (O), U$2.CE1
CLOCK: H.D1, J.U1
DAD+DST: E11.13 (A3), E16.9 (I), E28.8 (O), H.H1
DATA7: E9.4 (O), E17.5 (I1), U$2.BV1
DATA8: E32.5 (I1), E35.10 (O), U$2.DR1
DATA9: E32.7 (I1), E35.13 (O), U$2.DS1
DATA10: E32.11 (I0), E35.4 (O), U$2.DU1
DATA11: E32.9 (I0), E35.1 (O), U$2.DV1
DATA_TO_SC: E9.2 (I0), E16.10 (O), E25.4 (I0), E36.9 (S0), R9.1
DEFER: E20.12 (I1), U$2.DK2
DIV_12_L: E16.12 (O), H.N1
E: E25.9 (I0), U$2.DL2
EAE_INST: E2.2 (O), E3.5 (I3), E3.9 (I0), E28.1 (I0), E28.2 (I1), E28.11 (I2)
EIR2: E11.11 (A1), E15.6 (I5), E19.11 (A1), E22.8 (!Q), H.T2
EIR3: E11.10 (A0), E15.11 (I6), E19.10 (A0), E26.6 (!Q), H.S1
EX1: E1.8 (I0), E30.9 (Q)
EXEC_DIVIDE: E8.3 (I1), E8.4 (O), E33.4 (I1)
EXEC_MULTIPLY: E8.1 (O), E33.9 (I0)
FD_SET: E19.7 (O7), H.U2
FETCH: E21.11 (I0), U$2.DJ2
FE_SET: E1.10 (O), E19.9 (O8), H.V1
GND: C1.2, C2.2, C3.2, C4.2, C6.2, C7.2, C8.2, C9.2, C10.2, C11.2, C12.2, C14.2, C15.2, C16.2, C17.2, C18.2, C19.2, C20.2, C21.2, C22.2, C23.2, C24.2, C25.2, C26.2, C27.2, C28.2, C29.2, C30.2, C31.2, C32.2, C33.2, C34.2, C35.-, C36.-, C37.-, E1.7 (GND), E2.7 (GND), E3.7 (GND), E4.13 (GND), E6.7 (GND), E7.7 (GND), E8.7 (GND), E9.7 (GND), E10.7 (GND), E11.8 (GND), E12.7 (GND), E14.7 (GND), E15.7 (GND), E16.7 (GND), E17.1 (GND), E17.4 (I0), E17.6 (I0), E17.10 (I1), E17.11 (I0), E18.7 (GND), E19.8 (GND), E20.1 (GND), E20.10 (I1), E21.1 (GND), E21.10 (I1), E21.12 (I1), E22.7 (GND), E23.7 (GND), E24.7 (GND), E25.1 (GND), E25.7 (I1), E25.10 (I1), E26.7 (GND), E27.7 (GND), E28.7 (GND), E29.1 (GND), E29.4 (I0), E29.6 (I0), E29.10 (I1), E29.12 (I1), E30.7 (GND), E31.7 (GND), E32.1 (GND), E32.4 (I0), E32.6 (I0), E32.10 (I1), E32.12 (I1), E33.7 (GND), E34.1 (B), E34.8 (GND), E34.9 (D), E34.10 (C), E35.7 (GND), E36.7 (S1), E36.8 (GND), E37.8 (GND), H.J2, H.K2, H.L2, H.M2, H.N2, H.P2, H.R2, H.S2, J.C1, J.C2, J.E1, J.E2, J.H1, J.H2, J.R1, J.R2, J.T1, J.T2, J.V1, U$2.AC2, U$2.AF1, U$2.AF2, U$2.AN1, U$2.AN2, U$2.AT1, U$2.AT2, U$2.BC1, U$2.BC2, U$2.BF1, U$2.BF2, U$2.BN1, U$2.BN2, U$2.BT1, U$2.BT2, U$2.CC1, U$2.CC2, U$2.CF1, U$2.CF2, U$2.CN1, U$2.CN2, U$2.CT1, U$2.CT2, U$2.DC1, U$2.DC2, U$2.DF1, U$2.DF2, U$2.DN1, U$2.DN2, U$2.DT1, U$2.DT2
GTF+IND: H.A1, J.S1
INCR_SC: E37.5 (UP), H.K1
INIT: E20.9 (I0), U$2.CR1
INT_IN_PROG: E17.7 (I1), U$2.BP2
LAST_STEP_L: E33.6 (O), E33.8 (O), E33.12 (O), H.C1
LD_EIR: E6.3 (CLK), E6.11 (CLK), E10.3 (CLK), E10.11 (CLK), E12.8 (O), E14.3 (CLK), E14.11 (CLK), E18.3 (CLK), E18.11 (CLK), E22.3 (CLK), E22.11 (CLK), E26.3 (CLK), E26.11 (CLK), E28.13 (I2)
MA_MS_LC: E17.12 (I1), U$2.BH2
MD0: E6.2 (D), U$2.AK1
MD1: E6.12 (D), U$2.AL1
MD2: E10.2 (D), U$2.AM1
MD3: E10.12 (D), U$2.AP1
MD4: E14.2 (D), U$2.BK1
MD5: E14.12 (D), U$2.BL1
MD6: E18.2 (D), U$2.BM1
MD7: E18.12 (D), E25.5 (I1), U$2.BP1
MD8: E22.2 (D), E29.9 (I0), U$2.DK1
MD9: E22.12 (D), E29.11 (I0), U$2.DL1
MD10: E26.2 (D), E29.7 (I1), U$2.DM1
MD11: E26.12 (D), E29.5 (I1), U$2.DP1
MODEA: E2.9 (I), E4.10 (!Q), E19.14 (A4)
MODEB: E1.12 (I1), E2.8 (O), E28.10 (I1), H.A2, H.R1
unnamed: E6.6 (!Q), E7.2 (I1)
unnamed: E6.8 (!Q), E7.3 (I2)
unnamed: E14.5 (Q), E15.1 (I0), E23.1 (I0)
unnamed: E7.4 (I3), E10.6 (!Q)
unnamed: E7.5 (I4), E10.8 (!Q)
unnamed: E2.1 (I), E7.8 (O)
unnamed: E7.6 (I5), E26.8 (!Q)
unnamed: E14.9 (Q), E15.2 (I1), E23.2 (I1)
unnamed: E15.3 (I2), E18.6 (!Q), E19.13 (A3), E28.9 (I0)
unnamed: E15.4 (I3), E18.9 (Q)
unnamed: E15.5 (I4), E22.5 (Q)
unnamed: E18.5 (Q), E23.3 (I2)
unnamed: E18.8 (!Q), E23.4 (I3)
unnamed: E11.12 (A2), E19.12 (A2), E22.6 (!Q), E23.5 (I4)
unnamed: E22.9 (Q), E23.6 (I5)
unnamed: E23.11 (I6), E26.5 (Q)
unnamed: E31.3 (I1), E33.2 (I1), E33.3 (I0), E35.12 (I1), E37.6 (QC)
unnamed: E16.13 (I), E28.6 (O), E33.11 (I2), E33.13 (I2)
unnamed: E3.8 (O), E11.14 (A4), E19.15 (!CE)
unnamed: E2.12 (O), E4.12 (K)
unnamed: E2.10 (O), E4.9 (J)
unnamed: E3.4 (I2), E27.6 (O)
unnamed: E3.6 (O), E11.15 (!CE)
unnamed: E1.11 (I0), E30.6 (!Q), E31.9 (I1)
unnamed: E4.6 (CLK), E28.12 (O)
unnamed: E1.6 (I1), E21.14 (O)
unnamed: E1.3 (I1), E17.2 (O)
unnamed: E32.3 (O), E36.1 (A0)
unnamed: E32.2 (O), E36.6 (A1)
unnamed: E32.13 (O), E36.10 (A2)
unnamed: E32.14 (O), E36.15 (A3)
unnamed: E36.13 (F3), E37.15 (A)
unnamed: E36.12 (F2), E37.1 (B)
unnamed: E36.4 (F1), E37.10 (C)
unnamed: E36.3 (F0), E37.9 (D)
unnamed: E9.6 (I1), E31.2 (I0), E33.1 (I0), E34.3 (QA)
unnamed: E16.1 (I), E28.4 (I1), E35.2 (I0), E37.3 (QA)
unnamed: E28.5 (I2), E31.6 (I1), E35.5 (I0), E37.2 (QB)
unnamed: E17.13 (O), E27.10 (I1)
unnamed: E28.3 (I0), E31.5 (I0), E33.5 (I2), E35.9 (I1), E37.7 (QD)
unnamed: E9.11 (I0), E9.12 (I1), E25.3 (O)
unnamed: E9.1 (O), E9.13 (O), E34.15 (A), R10.1
unnamed: E9.3 (I1), E17.3 (O)
unnamed: E34.5 (UP), E37.12 (CO)
unnamed: E16.2 (O), E24.3 (I0)
unnamed: E24.4 (I1), E31.4 (O)
unnamed: E24.5 (I2), E31.1 (O), E33.10 (I1)
unnamed: E17.14 (O), E27.9 (I0)
unnamed: E16.5 (I), E27.8 (O)
unnamed: E1.2 (I0), E16.6 (O), E30.11 (CLK)
unnamed: E20.13 (O), E30.12 (D)
unnamed: E31.8 (I0), E31.13 (O)
unnamed: E16.4 (O), E31.12 (I1)
NEXT_LOC: E27.3 (O), H.P1
RESTART: H.H2, J.V2
ROM_11_L: E11.1 (O1), H.D2
ROM_12_L: E8.2 (I0), E8.5 (I0), E11.2 (O2), H.B2, R4.1
ROM_13_L: E11.3 (O3), H.L1
ROM_14_L: E8.6 (I1), E11.4 (O4), H.B1
ROM_15_L: E11.5 (O5), H.E2
ROM_17_L: E11.7 (O7), H.C2
ROM_19_L: E11.9 (O8), E31.11 (I0), R5.1
ROM_21_L: E16.11 (I), E19.1 (O1), E30.2 (D), R6.1
ROM_22_L: E19.2 (O2), H.J1
ROM_23_L: E8.9 (I1), E19.3 (O3), R7.1
ROM_24_L: E19.4 (O4), H.M1
ROM_25_L: E19.5 (O5), E25.12 (I1), R8.1
ROM_26_L: E19.6 (O6), E27.1 (I0), R2.1
RTF: H.T1, J.D1
SC_TO_DATA: E9.5 (I0), E25.13 (O), E35.3 (I1), E35.6 (I1), E35.8 (I0), E35.11 (I0)
SWAB: E2.11 (I), E3.1 (I0), E3.13 (I3), E23.8 (O)
SWBA: E2.13 (I), E3.2 (I1), E3.12 (I2), E15.8 (O)
TP1: E21.9 (I0), U$2.CD2
TP2: E12.9 (I0), U$2.CE2
TP2_D: E16.3 (I), E30.3 (CLK), H.F2
TP3: E25.6 (I0), U$2.CH2
TP4: E17.9 (I0), U$2.CJ2
TS3: E25.11 (I0), U$2.CM2
VCC: C1.1, C2.1, C3.1, C4.1, C6.1, C7.1, C8.1, C9.1, C10.1, C11.1, C12.1, C14.1, C15.1, C16.1, C17.1, C18.1, C19.1, C20.1, C21.1, C22.1, C23.1, C24.1, C25.1, C26.1, C27.1, C28.1, C29.1, C30.1, C31.1, C32.1, C33.1, C34.1, C35.+, C36.+, C37.+, E1.14 (VCC), E2.14 (VCC), E3.14 (VCC), E4.5 (VCC), E6.14 (VCC), E7.14 (VCC), E8.14 (VCC), E9.14 (VCC), E10.14 (VCC), E11.16 (VCC), E12.14 (VCC), E14.14 (VCC), E15.14 (VCC), E16.14 (VCC), E17.8 (VCC), E18.14 (VCC), E19.16 (VCC), E20.8 (VCC), E21.8 (VCC), E22.14 (VCC), E23.14 (VCC), E24.14 (VCC), E25.8 (VCC), E26.14 (VCC), E27.14 (VCC), E28.14 (VCC), E29.8 (VCC), E30.14 (VCC), E31.14 (VCC), E32.8 (VCC), E33.14 (VCC), E34.16 (VCC), E35.14 (VCC), E36.16 (VCC), E37.16 (VCC), R1.2, R2.2, R3.2, R4.2, R5.2, R6.2, R7.2, R8.2, R9.2, R10.2, R11.2, R13.2, U$2.AA2, U$2.BA2, U$2.CA2

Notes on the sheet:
E-CS-M8340-0-1
EAE Decoder and Step Counter
M8330B or later.
Connects to
M8341D or later

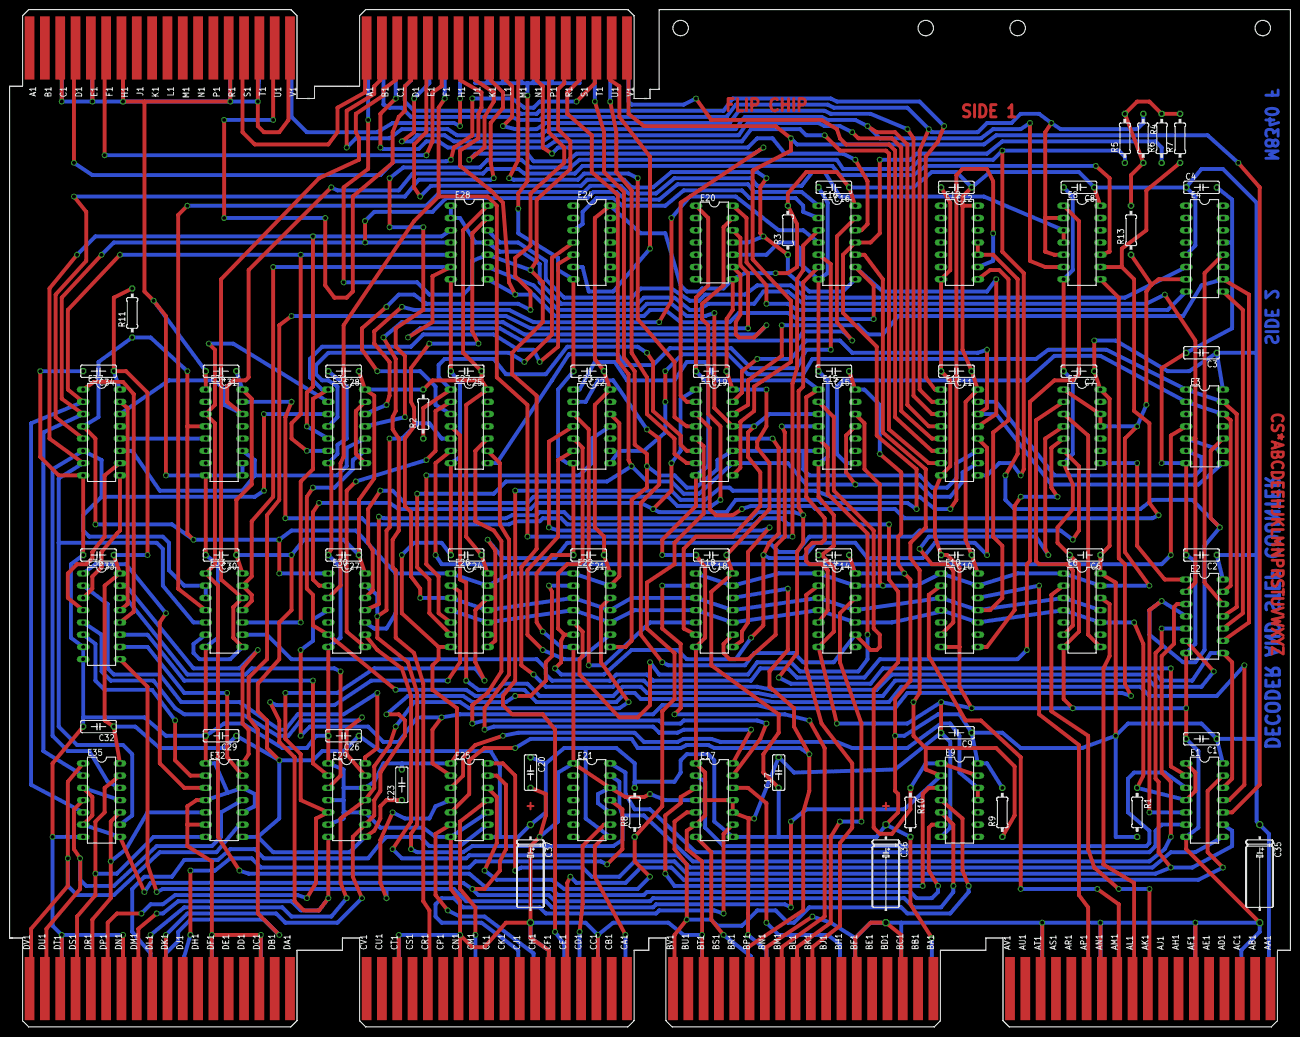
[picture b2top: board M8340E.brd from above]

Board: 2 copper layers, 265.4 x 210.8 mm, 85 parts (0 on the bottom side), 142 nets.
